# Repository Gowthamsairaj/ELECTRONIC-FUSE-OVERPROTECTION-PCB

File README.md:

View this project on [CADLAB.io](https://cadlab.io/project/29902). 

# Electronic Fuse (e-Fuse) & Over-Current Protection PCB

Comparator-Based Smart Load Disconnect for 24V Systems

---

## 📌 Project Overview
This project implements an electronic fuse (e-Fuse) system that protects a load from over-current and short-circuit conditions.

Instead of a traditional fuse that must be replaced after failure, this design detects excessive current in real time, disconnects the load using a MOSFET, and allows reset via a push button.

The board demonstrates current sensing, analog decision making, and power switching techniques used in industrial and embedded hardware.

---

## 🎯 Features
- Designed for 24V DC systems
- Real-time current monitoring
- Adjustable fault threshold
- Automatic load shutdown during over-current
- Manual reset using push button
- Fault indication LED
- Comparator-based fast response
- Reusable protection (no fuse replacement)

---

## 🧠 Working Principle
1. Load current flows through a shunt resistor.
2. Voltage across the shunt is proportional to current.
3. Comparator checks this voltage against a reference.
4. If current exceeds limit:
   - MOSFET is turned OFF
   - Load disconnects
   - Fault LED turns ON
5. Pressing reset allows system restart.

---

## 🔧 Main Components
- LM393 – Voltage comparator
- N-MOSFET – High current switching
- Shunt resistor – Current sensing
- Reference divider – Threshold setting
- Pull-up resistor – Comparator output
- LED – Fault indication
- Push button – Reset control

---

## ⚡ Electrical Flow
24V Input → Shunt → MOSFET → Load
↓
Comparator Decision → Shutdown

---

## 🛡 Protection Capabilities
- Over-current protection
- Short-circuit response
- Controlled restart
- Reduced downtime
- No consumable fuse element

---

## 📐 PCB Design Highlights
- High current path separated from signal area
- Wide copper for load current
- Kelvin-like sensing approach
- Clean comparator routing
- Designed with manufacturable rules
- ERC / DRC verified

---

## 🧪 Applications
- Industrial power distribution
- Robotics
- Battery systems
- Automotive electronics
- Embedded controllers
- Lab power outputs

---

## 🚀 Skills Demonstrated
- Current sensing techniques
- Analog comparator design
- MOSFET gate control
- Fault logic implementation
- Power electronics layout practice

---

## 🧰 Tools Used
- KiCad for schematic and PCB
- GitHub for version control

---

## 👤 Author
GOWTHAMA SAI RAJ R T

Electronics & Communication Engineering  
Focused on Embedded & Hardware Design

---

## 📜 License
Open-source for learning and academic use.

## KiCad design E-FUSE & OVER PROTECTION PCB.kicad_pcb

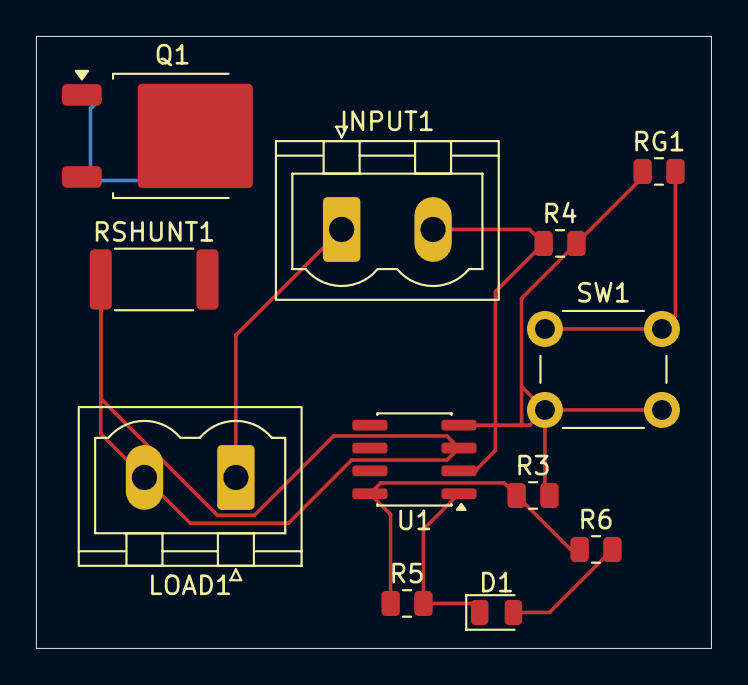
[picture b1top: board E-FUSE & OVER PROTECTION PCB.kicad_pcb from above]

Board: 2 copper layers, 37.5 x 34.0 mm, 12 parts (0 on the bottom side), 7 nets.

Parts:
D1: LED; LED_0805_2012Metric
INPUT1: Conn_01x02; PhoenixContact_MSTBVA_2,5_2-G-5,08_1x02_P5.08mm_Vertical
LOAD1: Conn_01x02; PhoenixContact_MSTBVA_2,5_2-G-5,08_1x02_P5.08mm_Vertical
Q1: Q_NMOS; TO-252-2
R3, R4, R5, R6: R; R_0805_2012Metric
RG1: R; R_0805_2012Metric
RSHUNT1: R; R_2512_6332Metric
SW1: SW_Push; SW_PUSH_6mm
U1: LM393; SOIC-8_3.9x4.9mm_P1.27mm

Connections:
/+5V: R3.1, R5.1, R6.1, U1.8 (V+)
/OUT: D1.1 (K), R5.2, U1.1
/VIN_24: INPUT1.1, LOAD1.1
GND: INPUT1.2, R3.2, R4.1, R4.2, RG1.1, SW1.2, U1.2 (-), U1.4 (V-)
unnamed: D1.2 (A), R6.2
unnamed: LOAD1.2, RSHUNT1.1, U1.3 (+)
unnamed: RG1.2, SW1.1

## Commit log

2026-02-07 E-FUSE & OVERPROTECTION PCB
2026-02-07 Backlink to CADLAB.io has been added.
2026-02-08 Revise README with project details and features
    Updated project title and added detailed project overview, features, working principle, main components, electrical flow, protection capabilities, PCB design highlights, applications, skills demonstr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
